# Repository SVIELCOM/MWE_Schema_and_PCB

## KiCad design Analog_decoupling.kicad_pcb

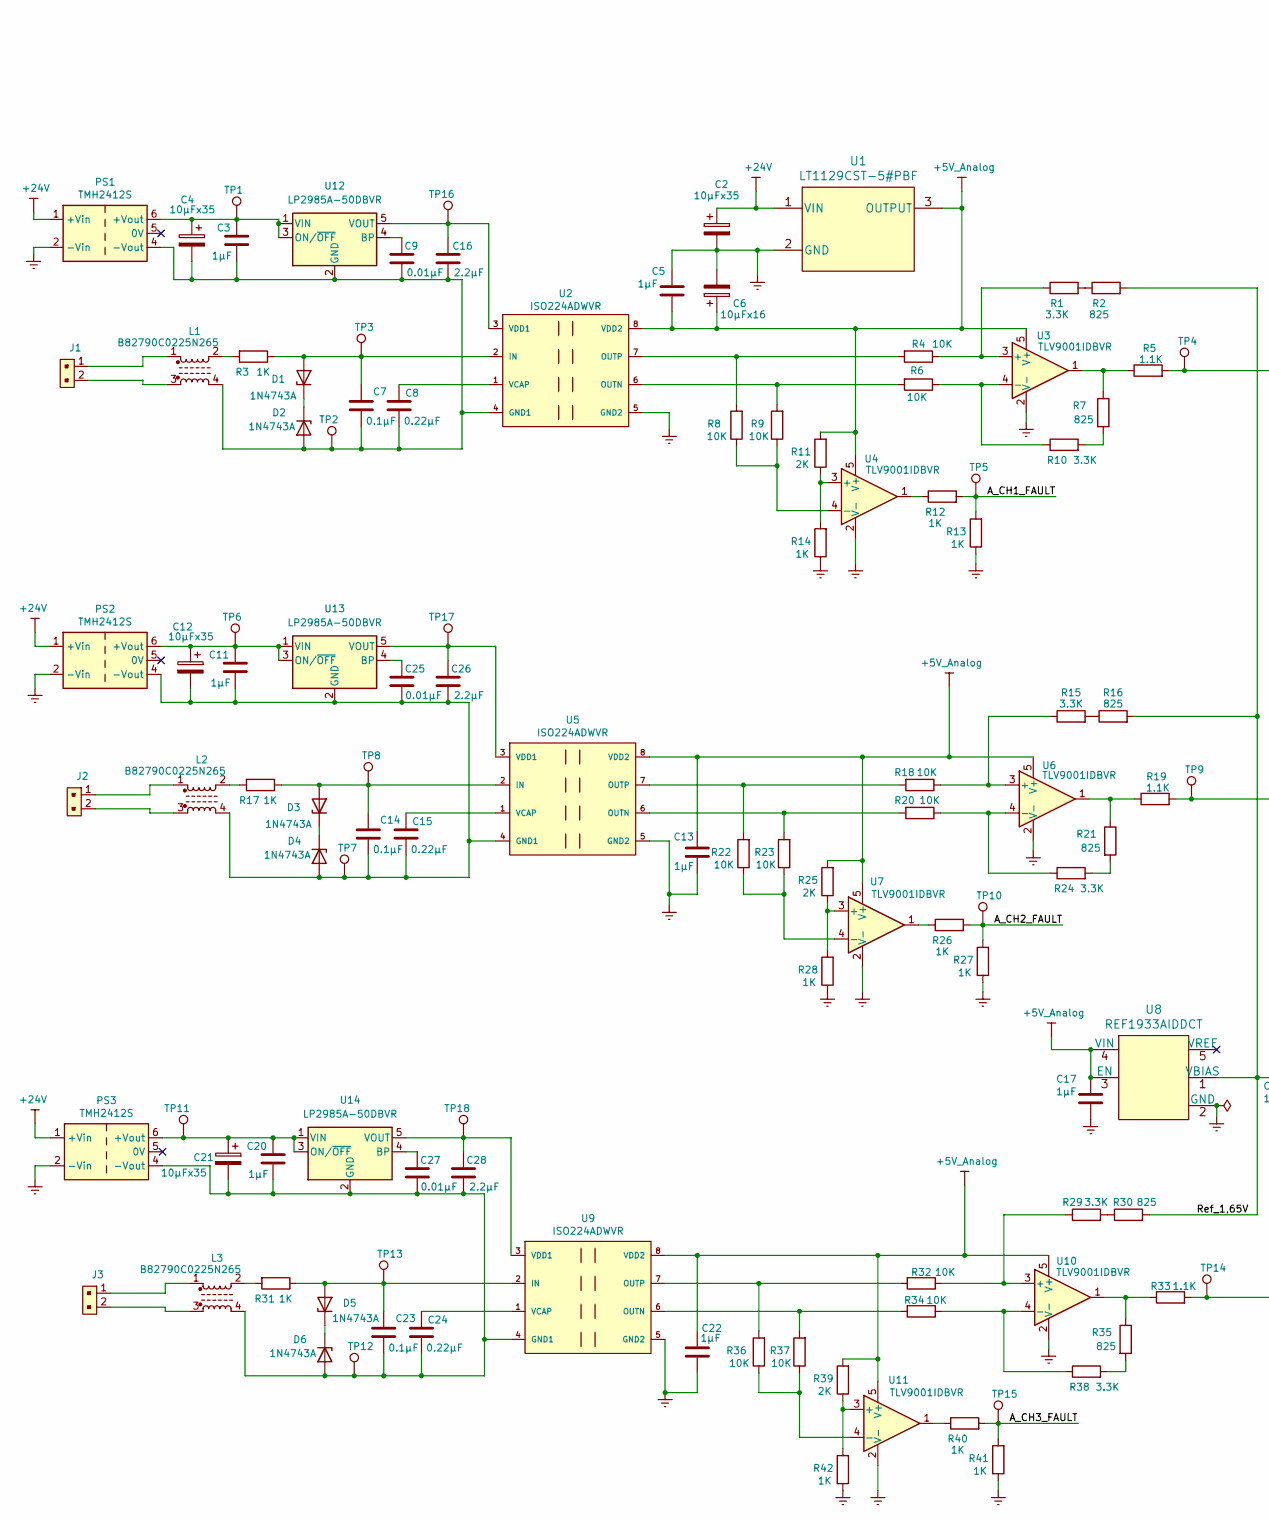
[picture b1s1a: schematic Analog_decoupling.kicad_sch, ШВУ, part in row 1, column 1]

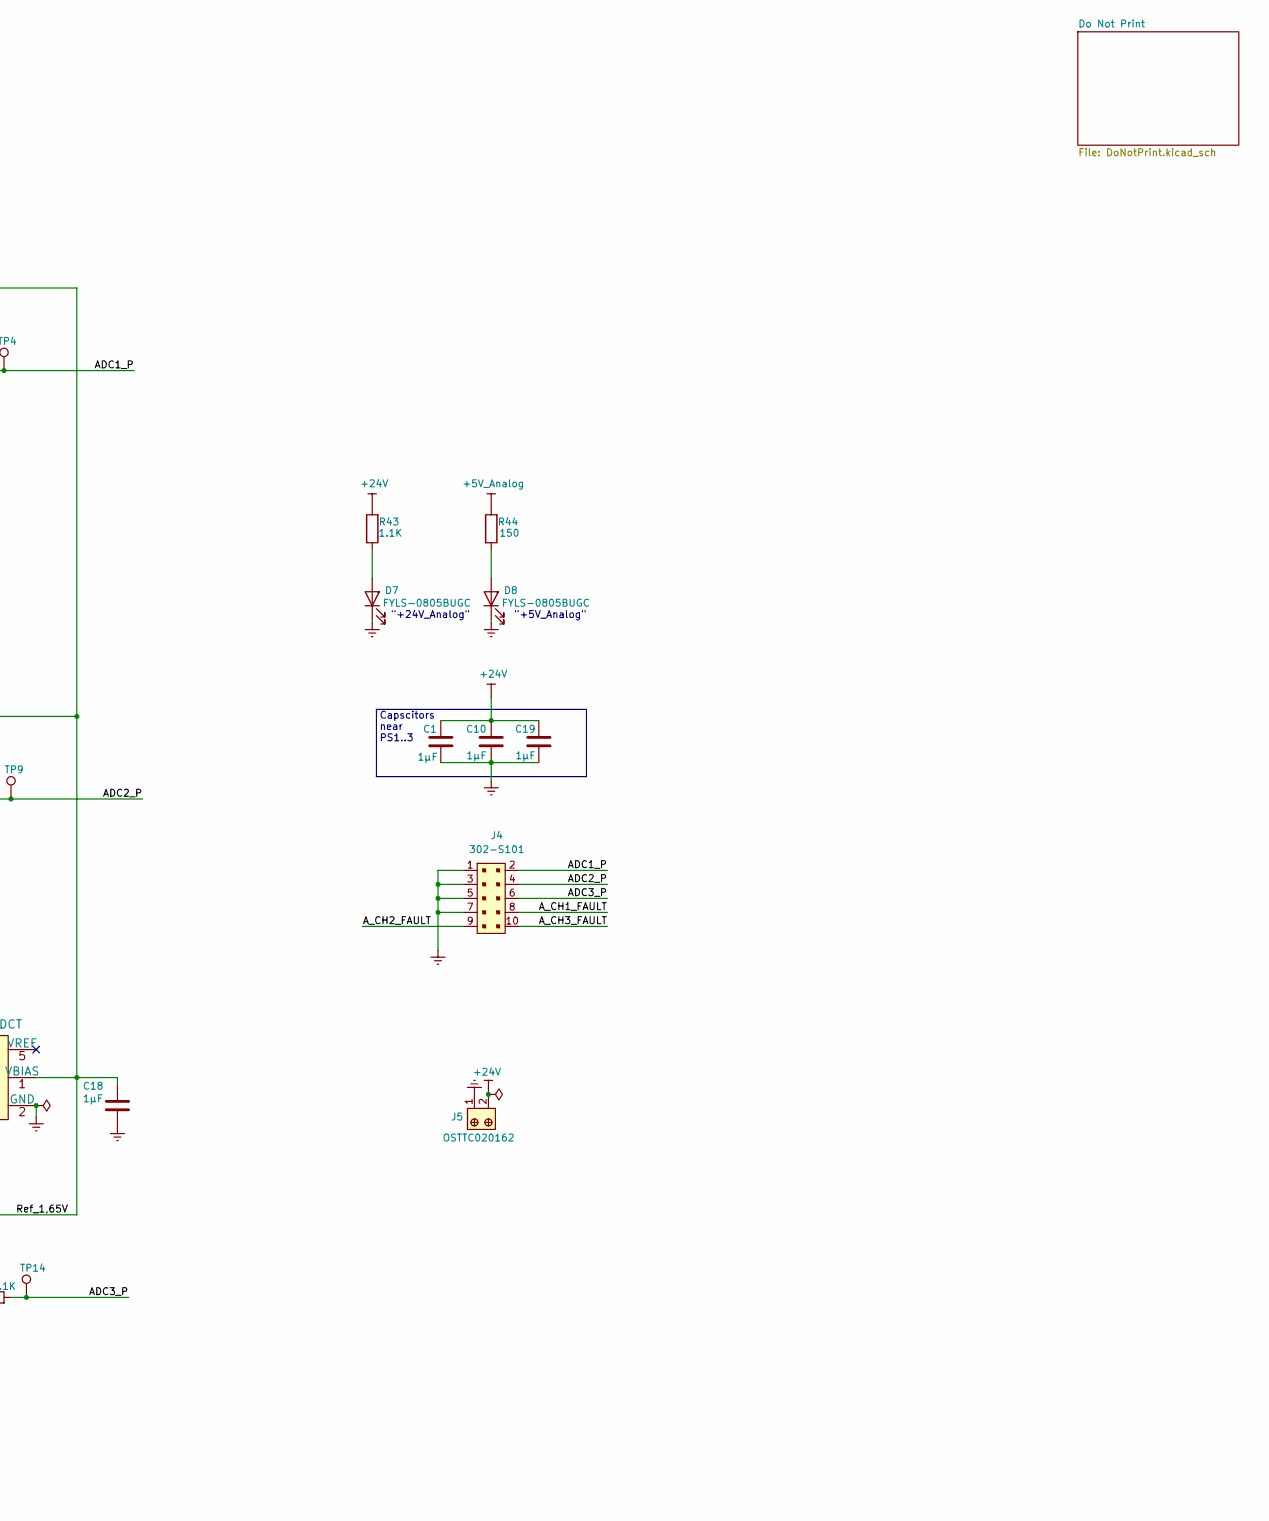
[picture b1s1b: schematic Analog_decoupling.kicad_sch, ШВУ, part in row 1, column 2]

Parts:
C1, C3, C5, C10, C11, C13, C17, C18, C19, C20, C22: 1µF; C_0603_1608Metric_Pad1.08x0.95mm_HandSolder
C2, C4, C12, C21: 10µFx35; CP_EIA-7343-30_AVX-N_Pad2.25x2.55mm_HandSolder
C6: 10µFx16; CP_EIA-3216-10_Kemet-I
C7, C14, C23: 0.1µF; C_0603_1608Metric_Pad1.08x0.95mm_HandSolder
C8, C15, C24: 0.22µF; C_0603_1608Metric_Pad1.08x0.95mm_HandSolder
C9, C25, C27: 0.01µF; C_0603_1608Metric
C16, C26, C28: 2.2µF; C_0603_1608Metric
D1, D2, D3, D4, D5, D6: 1N4743A; D_DO-41_SOD81_P10.16mm_Horizontal
D7, D8: FYLS-0805BUGC; LED_0805_2012Metric
J1, J2, J3: 22-23-2021; PinHeader_1x2_P2.54mm_Drill1.02mm; MPN 22-23-2021; Digi-Key_PN WM4200-ND
J4: 302-S101; PinHeader_2x5_P2.54mm_Drill1.2mm; MPN 302-S101; Digi-Key_PN ED1543-ND
J5: OSTTC020162; Term_Block_1x2_P5mm; MPN OSTTC020162; Digi-Key_PN ED2600-ND
L1, L2, L3: B82790C0225N265
PS1, PS2, PS3: TMH2412S; Converter_DCDC_XP_POWER-IAxxxxS_THT
R1, R10, R15, R24, R29, R38: 3.3K; R_0603_1608Metric
R2, R7, R16, R21, R30, R35: 825; R_0603_1608Metric
R3, R17, R31: 1K; R_Axial_DIN0207_L6.3mm_D2.5mm_P10.16mm_Horizontal
R4, R6, R8, R9, R18, R20, R22, R23, R32, R34, R36, R37: 10K; R_0805_2012Metric
R5, R19, R33, R43: 1.1K; R_0805_2012Metric
R11, R25, R39: 2K; R_0805_2012Metric
R12, R13, R14, R26, R27, R28, R40, R41, R42: 1K; R_0805_2012Metric
R44: 150; R_0805_2012Metric
TP1, TP2, TP3, TP4, TP5, TP6, TP7, TP8, TP9, TP10, TP11, TP12, TP13, TP14, TP15, TP16, TP17, TP18: TestPoint; TestPoint_Pad_D1.5mm
U1: LT1129CST-5#PBF; SOT-223-3_TabPin2
U2, U5, U9: ISO224ADWVR; Texas_Instruments-DWV0008A-0-0-IPC_A; voltage gain 0.001/3V/mV; mouser part number 595-ISO224ADWVR; digikey description IC ISOLATED 8SOIC
U3, U4, U6, U7, U10, U11: TLV9001IDBVR; SOT-23-5
U8: REF1933AIDDCT; SOT-23-5_HandSoldering
U12, U13, U14: LP2985A-50DBVR; SOT-23-5

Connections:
+5V_Analog: C5.2, C6.1, C13.2, C17.1, C22.2, R11.2, R25.2, R39.2, R44.2, U1.3 (OUTPUT), U2.8 (VDD2), U3.5 (V+), U4.5 (V+), U5.8 (VDD2), U6.5 (V+), U7.5 (V+), U8.3 (EN), U8.4 (VIN), U9.8 (VDD2), U10.5 (V+), U11.5 (V+)
+24V: C1.1, C2.1, C10.1, C19.1, J5.2, PS1.1 (+Vin), PS2.1 (+Vin), PS3.1 (+Vin), R43.2, U1.1 (VIN)
/ADC1_P: J4.2, R5.2, TP4.1
/ADC2_P: J4.4, R19.2, TP9.1
/ADC3_P: J4.6, R33.2, TP14.1
/A_CH1_FAULT: J4.8, R12.2, R13.2, TP5.1
/A_CH2_FAULT: J4.9, R26.2, R27.2, TP10.1
/A_CH3_FAULT: J4.10, R40.2, R41.2, TP15.1
/Ref_1,65V: C18.1, R2.2, R16.2, R30.2, U8.1 (VBIAS)
GNDREF: C1.2, C2.2, C5.1, C6.2, C10.2, C13.1, C17.2, C18.2, C19.2, C22.1, D7.1 (K), D8.1 (K), J4.1, J4.3, J4.5, J4.7, J5.1, PS1.2 (-Vin), PS2.2 (-Vin), PS3.2 (-Vin), R13.1, R14.1, R27.1, R28.1, R41.1, R42.1, U1.2 (GND), U2.5 (GND2), U3.2 (V-), U4.2 (V-), U5.5 (GND2), U6.2 (V-), U7.2 (V-), U8.2 (GND), U9.5 (GND2), U10.2 (V-), U11.2 (V-)
unnamed: C3.1, C4.1, PS1.6 (+Vout), TP1.1, U12.1 (VIN), U12.3 (ON/~OFF)
unnamed: C7.1, D1.2 (A), R3.1, TP3.1, U2.2 (IN)
unnamed: C8.1, U2.1 (VCAP)
unnamed: C9.1, U12.4 (BP)
unnamed: C11.1, C12.1, PS2.6 (+Vout), TP6.1, U13.1 (VIN), U13.3 (ON/~OFF)
unnamed: C11.2, C12.2, C14.2, C15.2, C25.2, C26.2, D4.2 (A), L2.4, PS2.4 (-Vout), TP7.1, U5.4 (GND1), U13.2 (GND)
unnamed: C14.1, D3.2 (A), R17.1, TP8.1, U5.2 (IN)
unnamed: C15.1, U5.1 (VCAP)
unnamed: C16.1, TP16.1, U2.3 (VDD1), U12.5 (VOUT)
unnamed: C3.2, C4.2, C7.2, C8.2, C9.2, C16.2, D2.2 (A), L1.4, PS1.4 (-Vout), TP2.1, U2.4 (GND1), U12.2 (GND)
unnamed: C20.1, C21.1, PS3.6 (+Vout), TP11.1, U14.1 (VIN), U14.3 (ON/~OFF)
unnamed: C20.2, C21.2, C23.2, C24.2, C27.2, C28.2, D6.2 (A), L3.4, PS3.4 (-Vout), TP12.1, U9.4 (GND1), U14.2 (GND)
unnamed: C23.1, D5.2 (A), R31.1, TP13.1, U9.2 (IN)
unnamed: C24.1, U9.1 (VCAP)
unnamed: C25.1, U13.4 (BP)
unnamed: C26.1, TP17.1, U5.3 (VDD1), U13.5 (VOUT)
unnamed: C27.1, U14.4 (BP)
unnamed: C28.1, TP18.1, U9.3 (VDD1), U14.5 (VOUT)
unnamed: D1.1 (K), D2.1 (K)
unnamed: D3.1 (K), D4.1 (K)
unnamed: D5.1 (K), D6.1 (K)
unnamed: D7.2 (A), R43.1
unnamed: D8.2 (A), R44.1
unnamed: J1.1, L1.1
unnamed: J1.2, L1.3
unnamed: J2.1, L2.1
unnamed: J2.2, L2.3
unnamed: J3.1, L3.1
unnamed: J3.2, L3.3
unnamed: L1.2, R3.2
unnamed: L2.2, R17.2
unnamed: L3.2, R31.2
unnamed: R1.1, R4.1, U3.3 (+)
unnamed: R1.2, R2.1
unnamed: R4.2, R8.2, U2.7 (OUTP)
unnamed: R5.1, R7.1, U3.1
unnamed: R6.2, R9.2, U2.6 (OUTN)
unnamed: R8.1, R9.1, U4.4 (-)
unnamed: R6.1, R10.1, U3.4 (-)
unnamed: R7.2, R10.2
unnamed: R11.1, R14.2, U4.3 (+)
unnamed: R12.1, U4.1
unnamed: R15.1, R18.1, U6.3 (+)
unnamed: R15.2, R16.1
unnamed: R18.2, R22.2, U5.7 (OUTP)
unnamed: R19.1, R21.1, U6.1
unnamed: R20.1, R24.1, U6.4 (-)
unnamed: R20.2, R23.2, U5.6 (OUTN)
unnamed: R21.2, R24.2
unnamed: R22.1, R23.1, U7.4 (-)
unnamed: R25.1, R28.2, U7.3 (+)
unnamed: R26.1, U7.1
unnamed: R29.1, R32.1, U10.3 (+)
unnamed: R29.2, R30.1
unnamed: R32.2, R36.2, U9.7 (OUTP)
unnamed: R33.1, R35.1, U10.1
unnamed: R34.1, R38.1, U10.4 (-)
unnamed: R34.2, R37.2, U9.6 (OUTN)
unnamed: R35.2, R38.2
unnamed: R36.1, R37.1, U11.4 (-)
unnamed: R39.1, R42.2, U11.3 (+)
unnamed: R40.1, U11.1

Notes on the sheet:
"+24V_Analog"
Capscitors near PS1..3
"+5V_Analog"

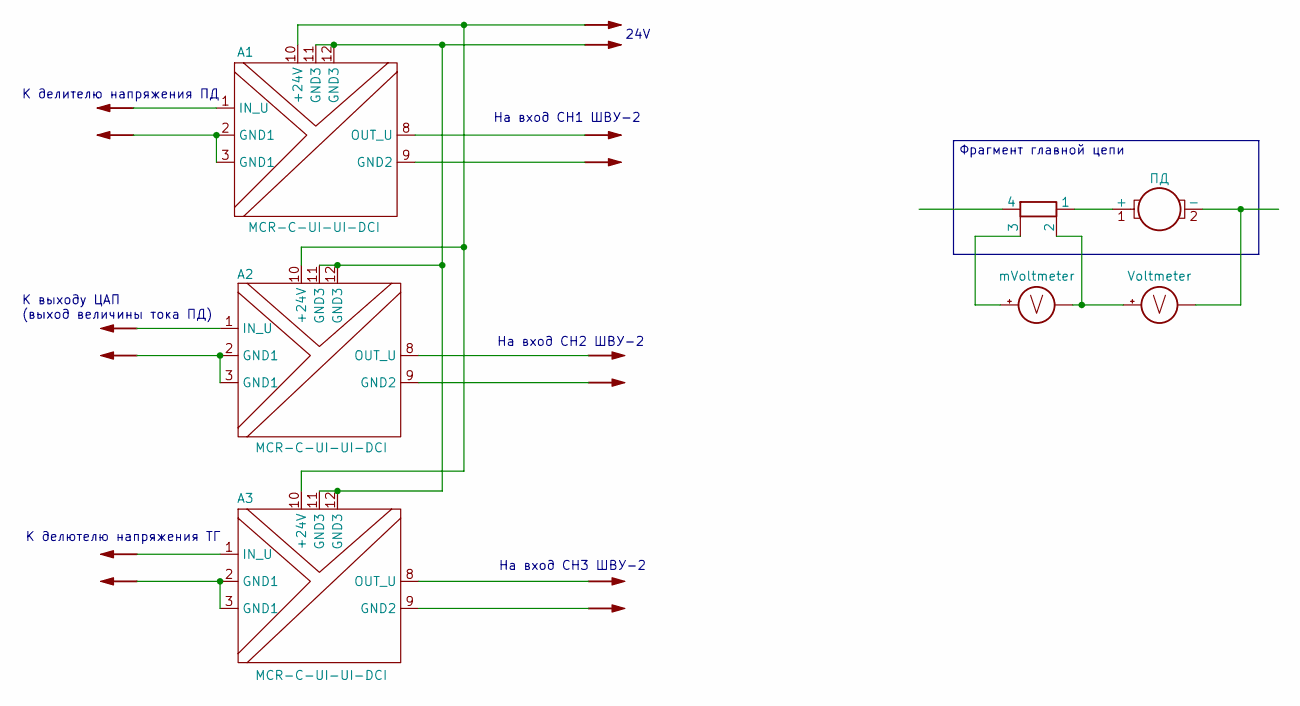
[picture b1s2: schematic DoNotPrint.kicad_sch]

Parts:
A1, A2, A3: MCR-C-UI-UI-DCI
M1: ПД
MES1: mVoltmeter
MES2: Voltmeter
R45: R_Shunt

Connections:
unnamed: A1.2 (GND1), A1.3 (GND1)
unnamed: A1.10 (+24V), A2.10 (+24V), A3.10 (+24V)
unnamed: A1.11 (GND3), A1.12 (GND3), A2.11 (GND3), A2.12 (GND3), A3.11 (GND3), A3.12 (GND3)
unnamed: A2.2 (GND1), A2.3 (GND1)
unnamed: A3.2 (GND1), A3.3 (GND1)
unnamed: M1.1 (+), R45.1
unnamed: M1.2 (-), MES2.1 (-)
unnamed: MES1.1 (-), MES2.2 (+), R45.2
unnamed: MES1.2 (+), R45.3

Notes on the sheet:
На вход CH3 ШВУ-2
24V
На вход CH1 ШВУ-2
На вход CH2 ШВУ-2
К делютелю напряжения ТГ
К делителю напряжения ПД
К выходу ЦАП (выход величины тока ПД)
Фрагмент главной цепи

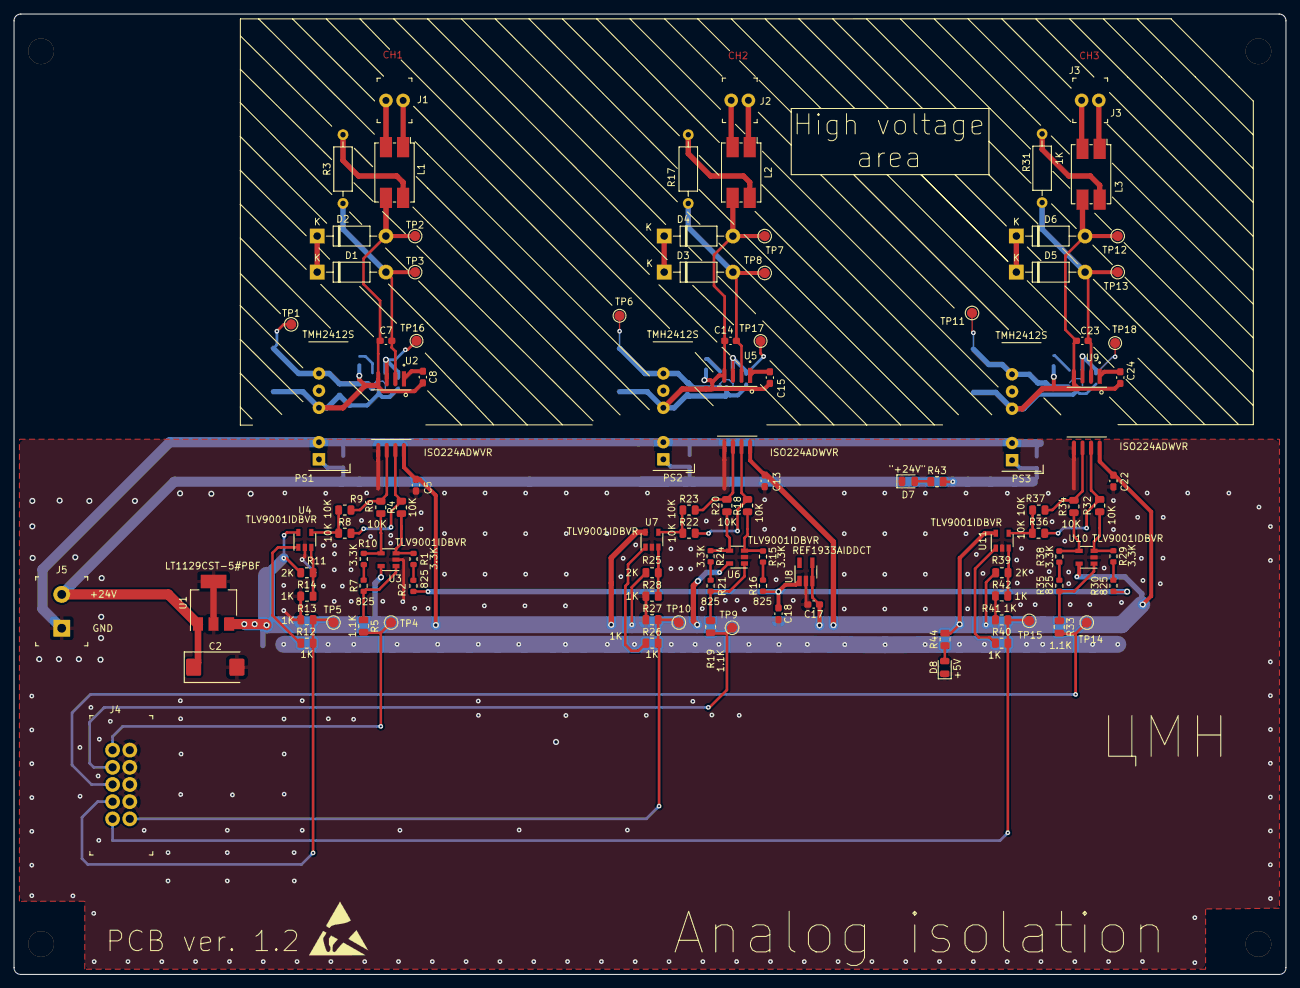
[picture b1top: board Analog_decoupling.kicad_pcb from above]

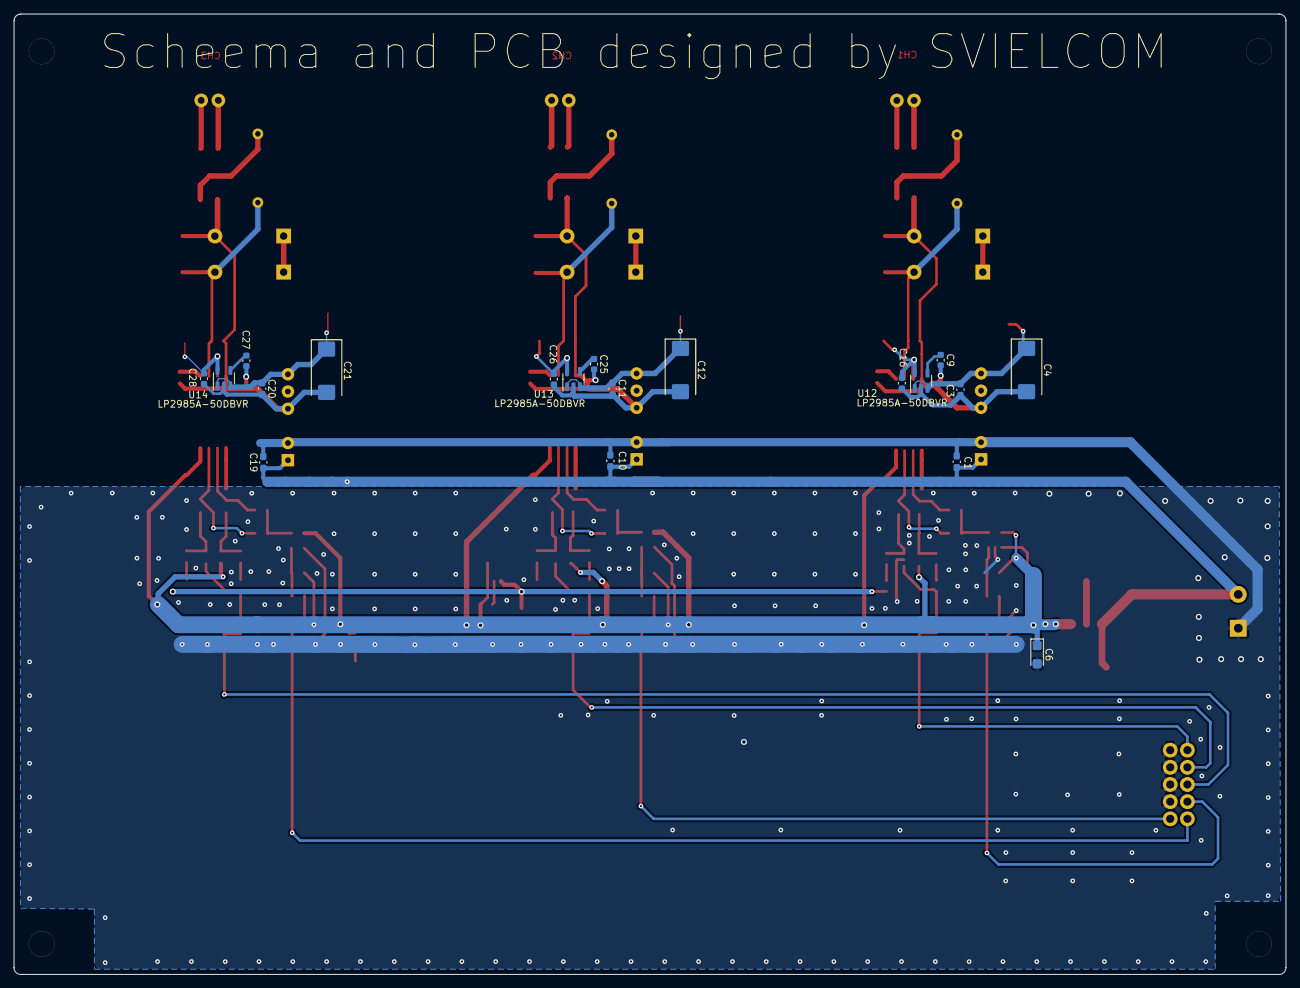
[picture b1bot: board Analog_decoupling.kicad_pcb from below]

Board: 2 copper layers, 188.1 x 142.0 mm, 123 parts (19 on the bottom side), 72 nets.

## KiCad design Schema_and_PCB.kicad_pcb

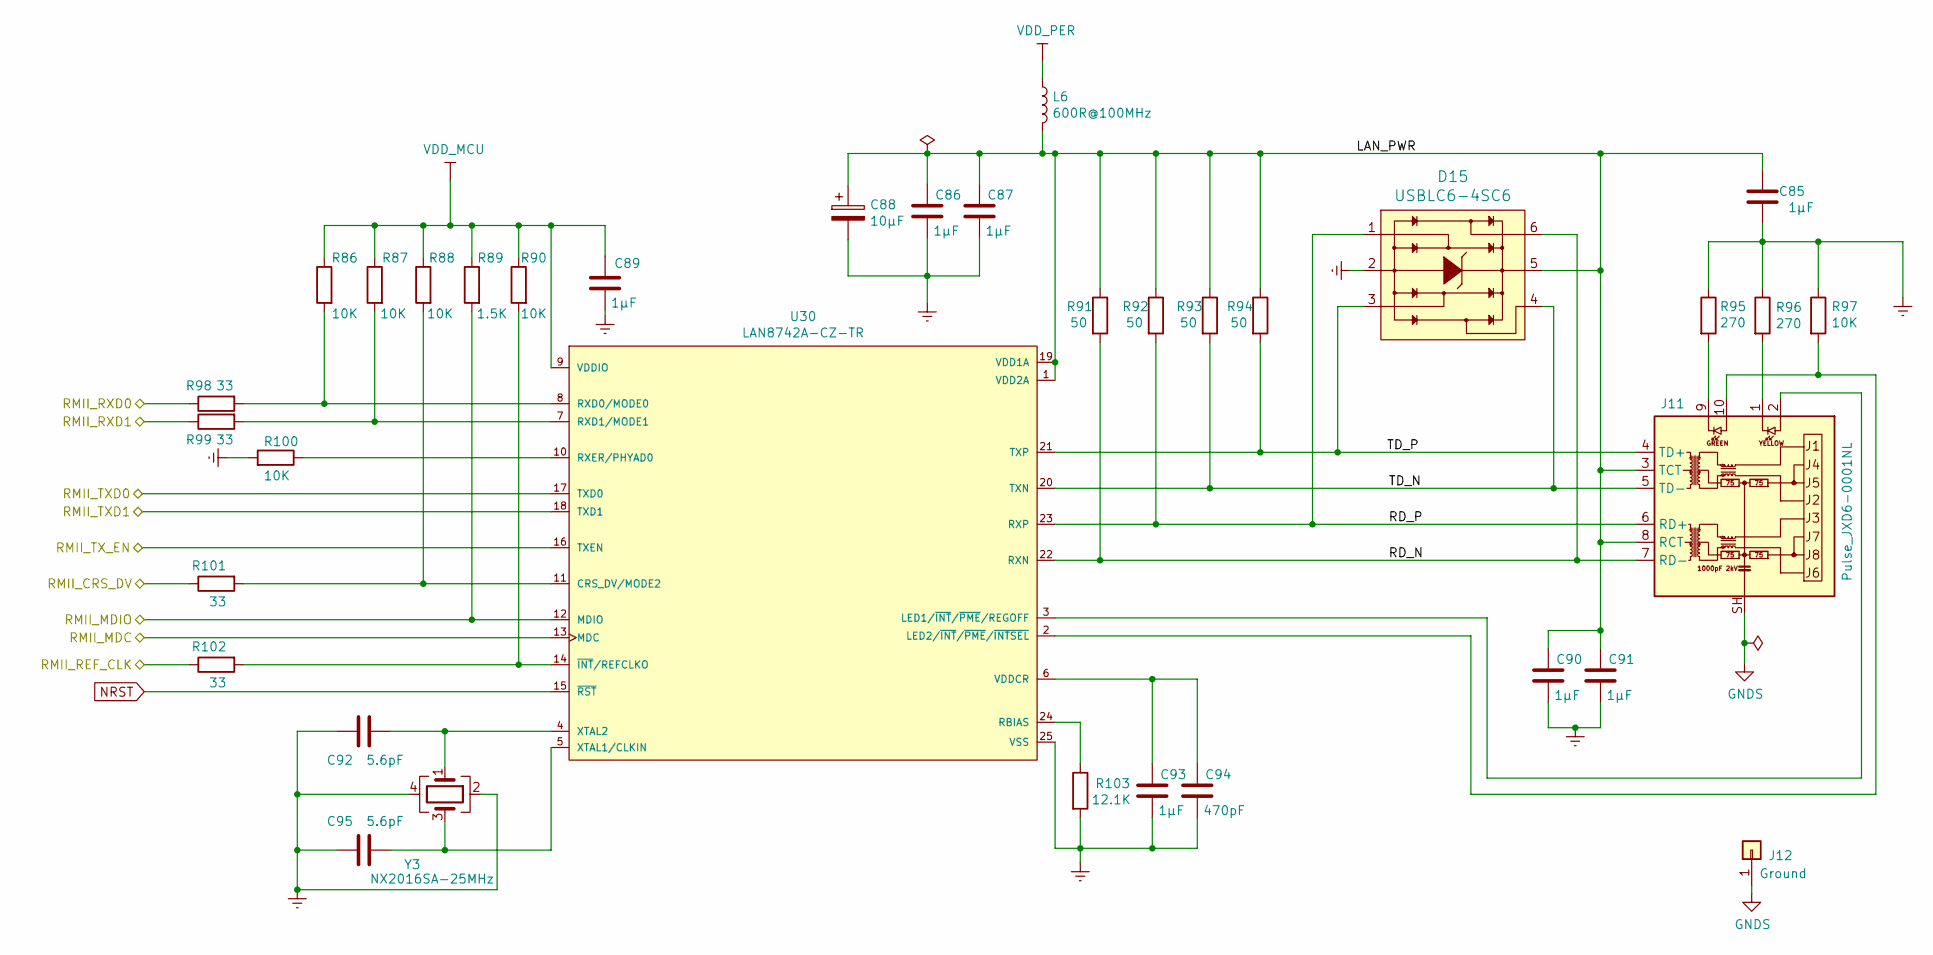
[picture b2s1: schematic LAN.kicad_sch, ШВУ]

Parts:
C85, C86, C87, C89, C90, C91, C93: 1µF; C_0603_1608Metric_Pad1.08x0.95mm_HandSolder
C88: 10µF; CP_EIA-3216-10_Kemet-I
C92, C95: 5.6pF; C_0603_1608Metric_Pad1.08x0.95mm_HandSolder
C94: 470pF; C_0603_1608Metric_Pad1.08x0.95mm_HandSolder
D15: USBLC6-4SC6; SOT-23-6_Handsoldering; MPN USBLC6-4SC6; Digi-Key_PN 497-4492-1-ND
J11: Pulse_JXD6-0001NL; RJ45_Pulse_JXD6-0001NL_Horizontal
J12: Ground; PinHeader_1x01_P2.54mm_Vertical
L6: 600R@100MHz; L_0805_2012Metric_Pad1.15x1.40mm_HandSolder
R86, R87, R90, R97, R100: 10K; R_0805_2012Metric_Pad1.20x1.40mm_HandSolder
R88: 10K; R_0805_2012Metric
R89: 1.5K; R_0805_2012Metric_Pad1.20x1.40mm_HandSolder
R91, R92, R93, R94: 50; R_0603_1608Metric_Pad0.98x0.95mm_HandSolder
R95, R96: 270; R_0805_2012Metric_Pad1.20x1.40mm_HandSolder
R98, R99, R101, R102: 33; R_0805_2012Metric_Pad1.20x1.40mm_HandSolder
R103: 12.1K; R_0805_2012Metric_Pad1.20x1.40mm_HandSolder
U30: LAN8742A-CZ-TR; Microchip-C04-143B-S4QFN-0-0-IPC_A; mouser part number 579-LAN8742A-CZ-TR; digikey description IC TRANSCEIVER 1/1 24SQFN
Y3: NX2016SA-25MHz; Crystal_SMD_2016-4Pin_2.0x1.6mm

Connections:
/LAN/LAN_PWR: C85.2, C86.1, C87.1, C88.1, C90.1, C91.1, D15.5, J11.3 (TCT), J11.8 (RCT), L6.2, R91.1, R92.1, R93.1, R94.1, U30.1 (VDD2A), U30.19 (VDD1A)
/LAN/RD_N: D15.6, J11.7 (RD-), R91.2, U30.22 (RXN)
/LAN/RD_P: D15.1, J11.6 (RD+), R92.2, U30.23 (RXP)
/LAN/RMII_CRS_DV: R101.1; also elsewhere on the board
/LAN/RMII_MDC: U30.13 (MDC); also elsewhere on the board
/LAN/RMII_MDIO: R89.2, U30.12 (MDIO); also elsewhere on the board
/LAN/RMII_REF_CLK: R102.1; also elsewhere on the board
/LAN/RMII_RXD0: R98.1; also elsewhere on the board
/LAN/RMII_RXD1: R99.1; also elsewhere on the board
/LAN/RMII_TXD0: U30.17 (TXD0); also elsewhere on the board
/LAN/RMII_TXD1: U30.18 (TXD1); also elsewhere on the board
/LAN/RMII_TX_EN: U30.16 (TXEN); also elsewhere on the board
/LAN/TD_N: D15.4, J11.5 (TD-), R93.2, U30.20 (TXN)
/LAN/TD_P: D15.3, J11.4 (TD+), R94.2, U30.21 (TXP)
GNDREF: C85.1, C86.2, C87.2, C88.2, C89.1, C90.2, C91.2, C92.2, C93.2, C94.2, C95.2, D15.2, R95.1, R96.1, R97.1, R100.2, R103.2, U30.25 (VSS), Y3.2, Y3.4; also elsewhere on the board
GNDS: J11.SH, J12.1
NRST: U30.15 (~RST); also elsewhere on the board
unnamed: C92.1, U30.4 (XTAL2), Y3.1
unnamed: C93.1, C94.1, U30.6 (VDDCR)
unnamed: C95.1, U30.5 (XTAL1/CLKIN), Y3.3
unnamed: J11.1, R96.2
unnamed: J11.2, U30.3 (LED1/~INT/~PME/REGOFF)
unnamed: J11.9, R95.2
unnamed: J11.10, R97.2, U30.2 (LED2/~INT/~PME/~INTSEL)
unnamed: R86.2, R98.2, U30.8 (RXD0/MODE0)
unnamed: R87.2, R99.2, U30.7 (RXD1/MODE1)
unnamed: R100.1, U30.10 (RXER/PHYAD0)
unnamed: R88.2, R101.2, U30.11 (CRS_DV/MODE2)
unnamed: R90.2, R102.2, U30.14 (~INT/REFCLKO)
unnamed: R103.1, U30.24 (RBIAS)
VDD_MCU: C89.2, R86.1, R87.1, R88.1, R89.1, R90.1, U30.9 (VDDIO); also elsewhere on the board
VDD_PER: L6.1; also elsewhere on the board

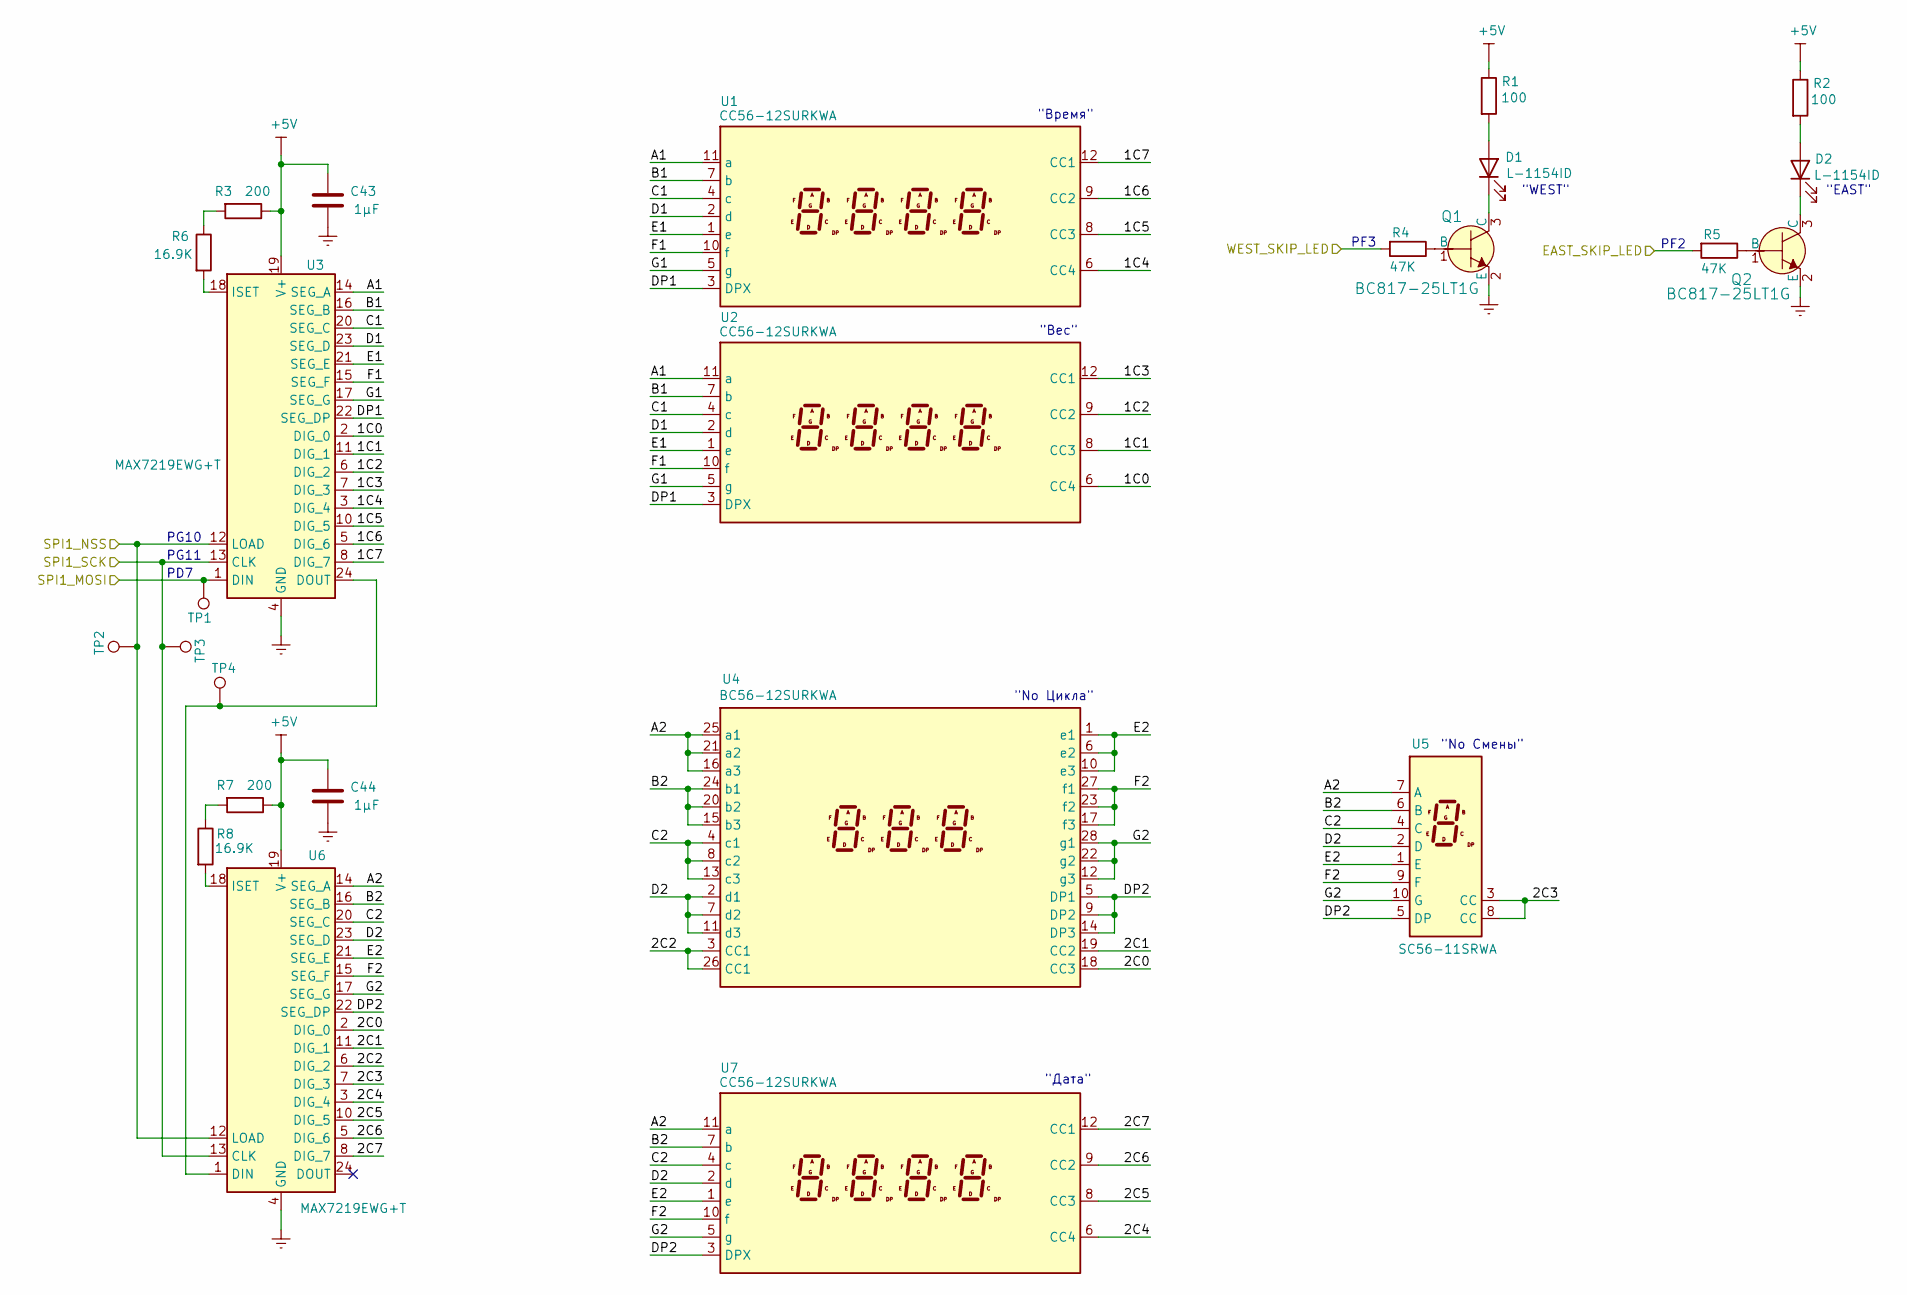
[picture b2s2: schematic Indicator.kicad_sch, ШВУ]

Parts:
C43, C44: 1µF; C_0603_1608Metric_Pad1.08x0.95mm_HandSolder
D1, D2: L-1154ID; LED_D3.0mm
Q1, Q2: BC817-25LT1G; SOT-23-3; MPN BC817-25LT1G; Digi-Key_PN BC817-25LT1GOSCT-ND
R1, R2: 100; R_0805_2012Metric_Pad1.20x1.40mm_HandSolder
R3, R7: 200; R_0805_2012Metric_Pad1.20x1.40mm_HandSolder
R4, R5: 47K; R_0805_2012Metric_Pad1.20x1.40mm_HandSolder
R6, R8: 16.9K; R_0805_2012Metric_Pad1.20x1.40mm_HandSolder
TP1, TP2, TP3, TP4: TestPoint; TestPoint_Pad_D1.5mm
U1, U2, U7: CC56-12SURKWA; CA56-12SURKWA
U3, U6: MAX7219EWG+T; SOIC-24W_7.5x15.4mm_P1.27mm
U4: BC56-12SURKWA; BC56-11SURKWA
U5: SC56-11SRWA; 7SegmentLED_LTS6760_LTS6780

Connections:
/Indicator/1C0: U2.6 (CC4), U3.2 (DIG_0)
/Indicator/1C1: U2.8 (CC3), U3.11 (DIG_1)
/Indicator/1C2: U2.9 (CC2), U3.6 (DIG_2)
/Indicator/1C3: U2.12 (CC1), U3.7 (DIG_3)
/Indicator/1C4: U1.6 (CC4), U3.3 (DIG_4)
/Indicator/1C5: U1.8 (CC3), U3.10 (DIG_5)
/Indicator/1C6: U1.9 (CC2), U3.5 (DIG_6)
/Indicator/1C7: U1.12 (CC1), U3.8 (DIG_7)
/Indicator/2C0: U4.18 (CC3), U6.2 (DIG_0)
/Indicator/2C1: U4.19 (CC2), U6.11 (DIG_1)
/Indicator/2C2: U4.3 (CC1), U4.26 (CC1), U6.6 (DIG_2)
/Indicator/2C3: U5.3 (CC), U5.8 (CC), U6.7 (DIG_3)
/Indicator/2C4: U6.3 (DIG_4), U7.6 (CC4)
/Indicator/2C5: U6.10 (DIG_5), U7.8 (CC3)
/Indicator/2C6: U6.5 (DIG_6), U7.9 (CC2)
/Indicator/2C7: U6.8 (DIG_7), U7.12 (CC1)
/Indicator/A1: U1.11 (a), U2.11 (a), U3.14 (SEG_A)
/Indicator/A2: U4.16 (a3), U4.21 (a2), U4.25 (a1), U5.7 (A), U6.14 (SEG_A), U7.11 (a)
/Indicator/B1: U1.7 (b), U2.7 (b), U3.16 (SEG_B)
/Indicator/B2: U4.15 (b3), U4.20 (b2), U4.24 (b1), U5.6 (B), U6.16 (SEG_B), U7.7 (b)
/Indicator/C1: U1.4 (c), U2.4 (c), U3.20 (SEG_C)
/Indicator/C2: U4.4 (c1), U4.8 (c2), U4.13 (c3), U5.4 (C), U6.20 (SEG_C), U7.4 (c)
/Indicator/D1: U1.2 (d), U2.2 (d), U3.23 (SEG_D)
/Indicator/D2: U4.2 (d1), U4.7 (d2), U4.11 (d3), U5.2 (D), U6.23 (SEG_D), U7.2 (d)
/Indicator/DP1: U1.3 (DPX), U2.3 (DPX), U3.22 (SEG_DP)
/Indicator/DP2: U4.5 (DP1), U4.9 (DP2), U4.14 (DP3), U5.5 (DP), U6.22 (SEG_DP), U7.3 (DPX)
/Indicator/E1: U1.1 (e), U2.1 (e), U3.21 (SEG_E)
/Indicator/E2: U4.1 (e1), U4.6 (e2), U4.10 (e3), U5.1 (E), U6.21 (SEG_E), U7.1 (e)
/Indicator/EAST_SKIP_LED: R5.2; also elsewhere on the board
/Indicator/F1: U1.10 (f), U2.10 (f), U3.15 (SEG_F)
/Indicator/F2: U4.17 (f3), U4.23 (f2), U4.27 (f1), U5.9 (F), U6.15 (SEG_F), U7.10 (f)
/Indicator/G1: U1.5 (g), U2.5 (g), U3.17 (SEG_G)
/Indicator/G2: U4.12 (g3), U4.22 (g2), U4.28 (g1), U5.10 (G), U6.17 (SEG_G), U7.5 (g)
/Indicator/SPI1_MOSI: TP1.1, U3.1 (DIN); also elsewhere on the board
/Indicator/SPI1_NSS: TP2.1, U3.12 (LOAD), U6.12 (LOAD); also elsewhere on the board
/Indicator/SPI1_SCK: TP3.1, U3.13 (CLK), U6.13 (CLK); also elsewhere on the board
/Indicator/WEST_SKIP_LED: R4.2; also elsewhere on the board
GNDREF: C43.2, C44.2, Q1.2 (E), Q2.2 (E), U3.4 (GND), U3.9 (GND), U6.4 (GND), U6.9 (GND); also elsewhere on the board
unnamed: D1.1 (K), Q1.3 (C)
unnamed: D1.2 (A), R1.2
unnamed: D2.1 (K), Q2.3 (C)
unnamed: D2.2 (A), R2.2
unnamed: Q1.1 (B), R4.1
unnamed: Q2.1 (B), R5.1
unnamed: R3.2, R6.1
unnamed: R6.2, U3.18 (ISET)
unnamed: R7.2, R8.1
unnamed: R8.2, U6.18 (ISET)
unnamed: TP4.1, U3.24 (DOUT), U6.1 (DIN)

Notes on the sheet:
"Вес"
"Дата"
"Время"
"EAST"
PG10
PG11
"WEST"
PD7
"No Смены"
"No Цикла"
PF3
PF2

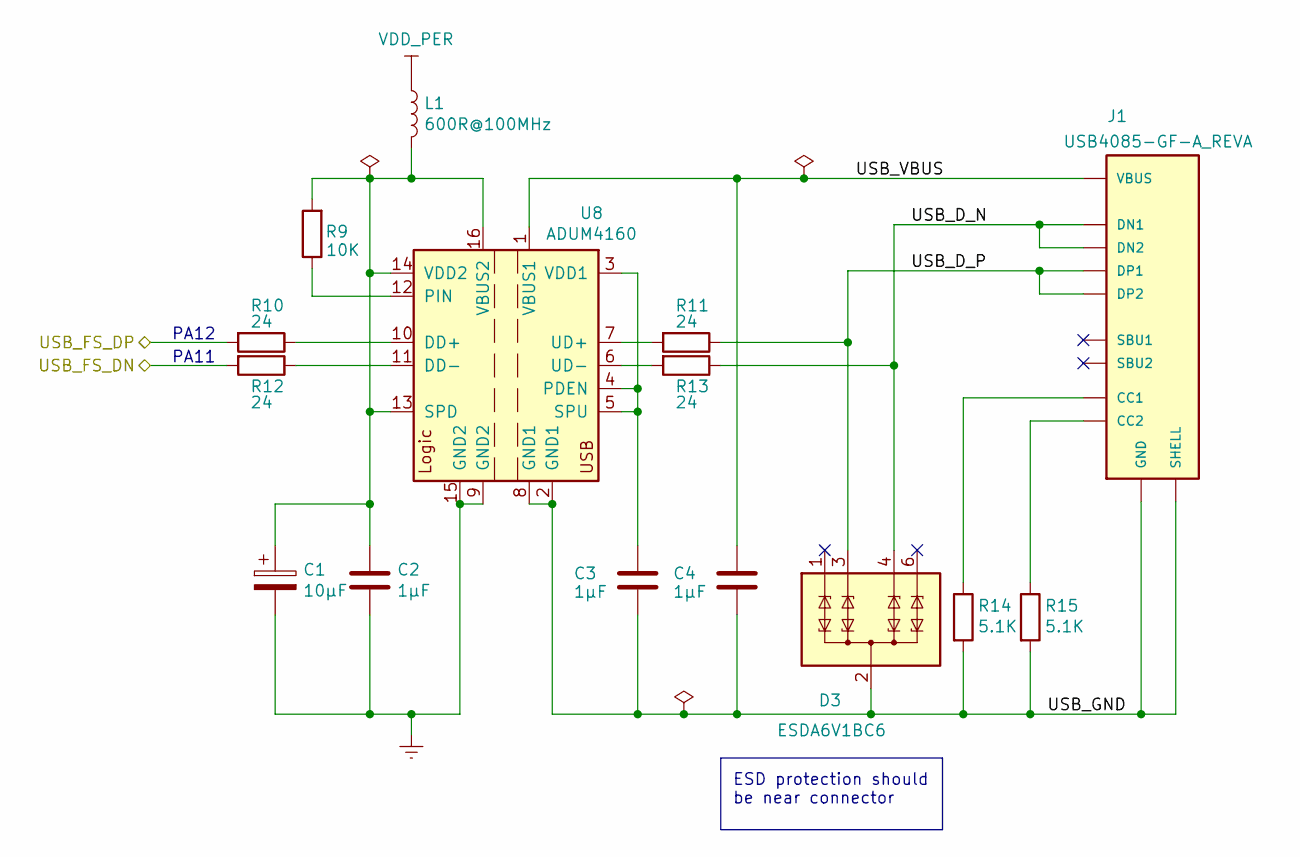
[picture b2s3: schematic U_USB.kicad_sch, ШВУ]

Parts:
C1: 10µF; CP_EIA-3216-10_Kemet-I
C2, C3, C4: 1µF; C_0603_1608Metric_Pad1.08x0.95mm_HandSolder
D3: ESDA6V1BC6; SOT-23-6
J1: USB4085-GF-A_REVA; GCT_USB4085-GF-A_REVA; PARTREV A2
L1: 600R@100MHz; L_0805_2012Metric_Pad1.15x1.40mm_HandSolder
R9: 10K; R_0805_2012Metric_Pad1.20x1.40mm_HandSolder
R10, R11, R12, R13: 24; R_0805_2012Metric_Pad1.20x1.40mm_HandSolder
R14, R15: 5.1K; R_0805_2012Metric_Pad1.20x1.40mm_HandSolder
U8: ADUM4160; SOIC-16W_7.5x10.3mm_P1.27mm

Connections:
/Microcontroller/USB_FS_DN: R12.2; also elsewhere on the board
/Microcontroller/USB_FS_DP: R10.2; also elsewhere on the board
/USB/USB_D_N: D3.4 (TVS3), J1.A7 (DN1), J1.B7 (DN2), R13.1
/USB/USB_D_P: D3.3 (TVS2), J1.A6 (DP1), J1.B6 (DP2), R11.1
/USB/USB_GND: C3.2, C4.2, D3.2 (COM), D3.5 (COM), J1.A1 (GND), J1.A12 (GND), J1.B1 (GND), J1.B12 (GND), J1.P1 (SHELL), J1.P2 (SHELL), J1.P3 (SHELL), J1.P4 (SHELL), R14.2, R15.2, U8.2 (GND1), U8.8 (GND1)
/USB/USB_VBUS: C4.1, J1.A4 (VBUS), J1.A9 (VBUS), J1.B4 (VBUS), J1.B9 (VBUS), U8.1 (VBUS1)
GNDREF: C1.2, C2.2, U8.9 (GND2), U8.15 (GND2); also elsewhere on the board
unnamed: C1.1, C2.1, L1.2, R9.2, U8.13 (SPD), U8.14 (VDD2), U8.16 (VBUS2)
unnamed: C3.1, U8.3 (VDD1), U8.4 (PDEN), U8.5 (SPU)
unnamed: J1.A5 (CC1), R14.1
unnamed: J1.B5 (CC2), R15.1
unnamed: R9.1, U8.12 (PIN)
unnamed: R10.1, U8.10 (DD+)
unnamed: R11.2, U8.7 (UD+)
unnamed: R12.1, U8.11 (DD-)
unnamed: R13.2, U8.6 (UD-)
VDD_PER: L1.1; also elsewhere on the board

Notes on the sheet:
PA11
PA12
ESD protection should be near connector

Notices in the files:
parts and their libraries:
Copyright 2016 Accelerated Designs. All rights reserved.
